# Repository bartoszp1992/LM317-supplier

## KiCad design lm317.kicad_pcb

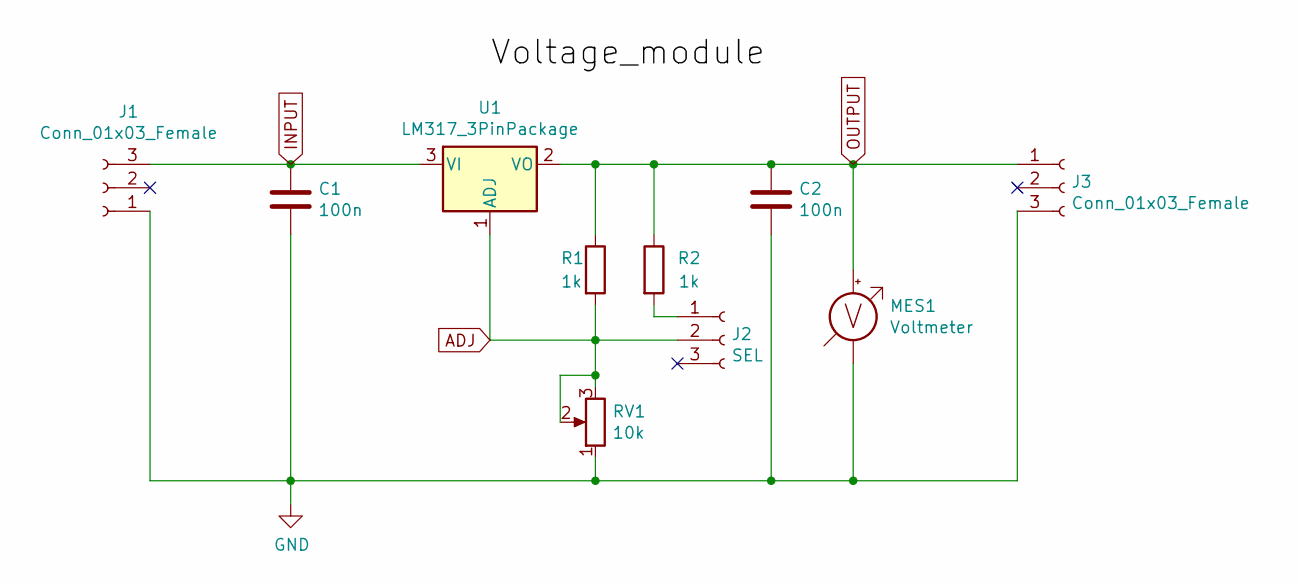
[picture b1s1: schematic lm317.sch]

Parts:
C1, C2: 100n; C_0603_1608Metric
J1, J3: Conn_01x03_Female; PinHeader_1x03_P2.54mm_Horizontal
J2: SEL; PinHeader_1x03_P2.54mm_Vertical
MES1: Voltmeter; PinHeader_1x02_P2.54mm_Vertical
R1, R2: 1k; R_0603_1608Metric
RV1: 10k; Potentiometer_ACP_CA9-H5_Horizontal
U1: LM317_3PinPackage; TO-220-3_Horizontal_TabDown

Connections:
ADJ: J2.2, R1.2, RV1.2, RV1.3, U1.1 (ADJ)
GND: C1.2, C2.2, J1.1, J3.3, MES1.1 (-), RV1.1
INPUT: C1.1, J1.3, U1.3 (VI)
unnamed: J2.1, R2.2
OUTPUT: C2.1, J3.1, MES1.2 (+), R1.1, R2.1, U1.2 (VO)

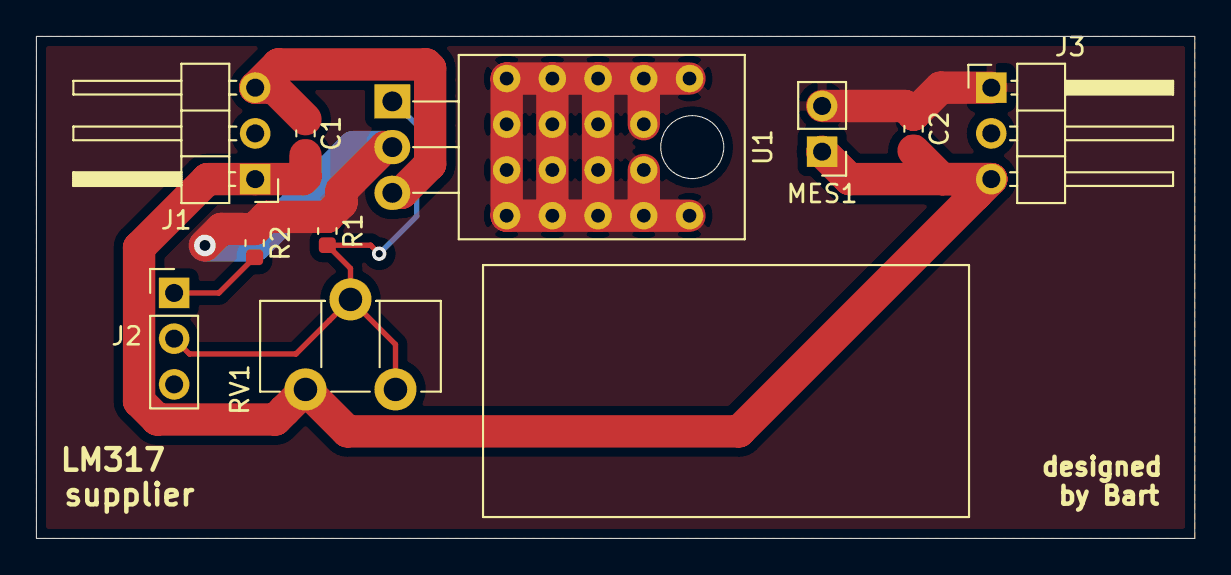
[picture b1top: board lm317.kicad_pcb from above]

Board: 2 copper layers, 64.3 x 27.9 mm, 10 parts (0 on the bottom side), 5 nets.

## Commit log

2020-09-11 initial
